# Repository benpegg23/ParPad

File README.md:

# ParPad

**ParPad** is an STM32-based macropad featuring a 3×3 layout and two rotary encoders.  

## Features

- 3×3 mechanical key matrix
- Dual EC11 rotary encoders with push functionality
- Cherry MX switch support
- USB-C connectivity
- STM32F072C8T6 Microcontroller
- Custom firmware (coming soon)

## Images

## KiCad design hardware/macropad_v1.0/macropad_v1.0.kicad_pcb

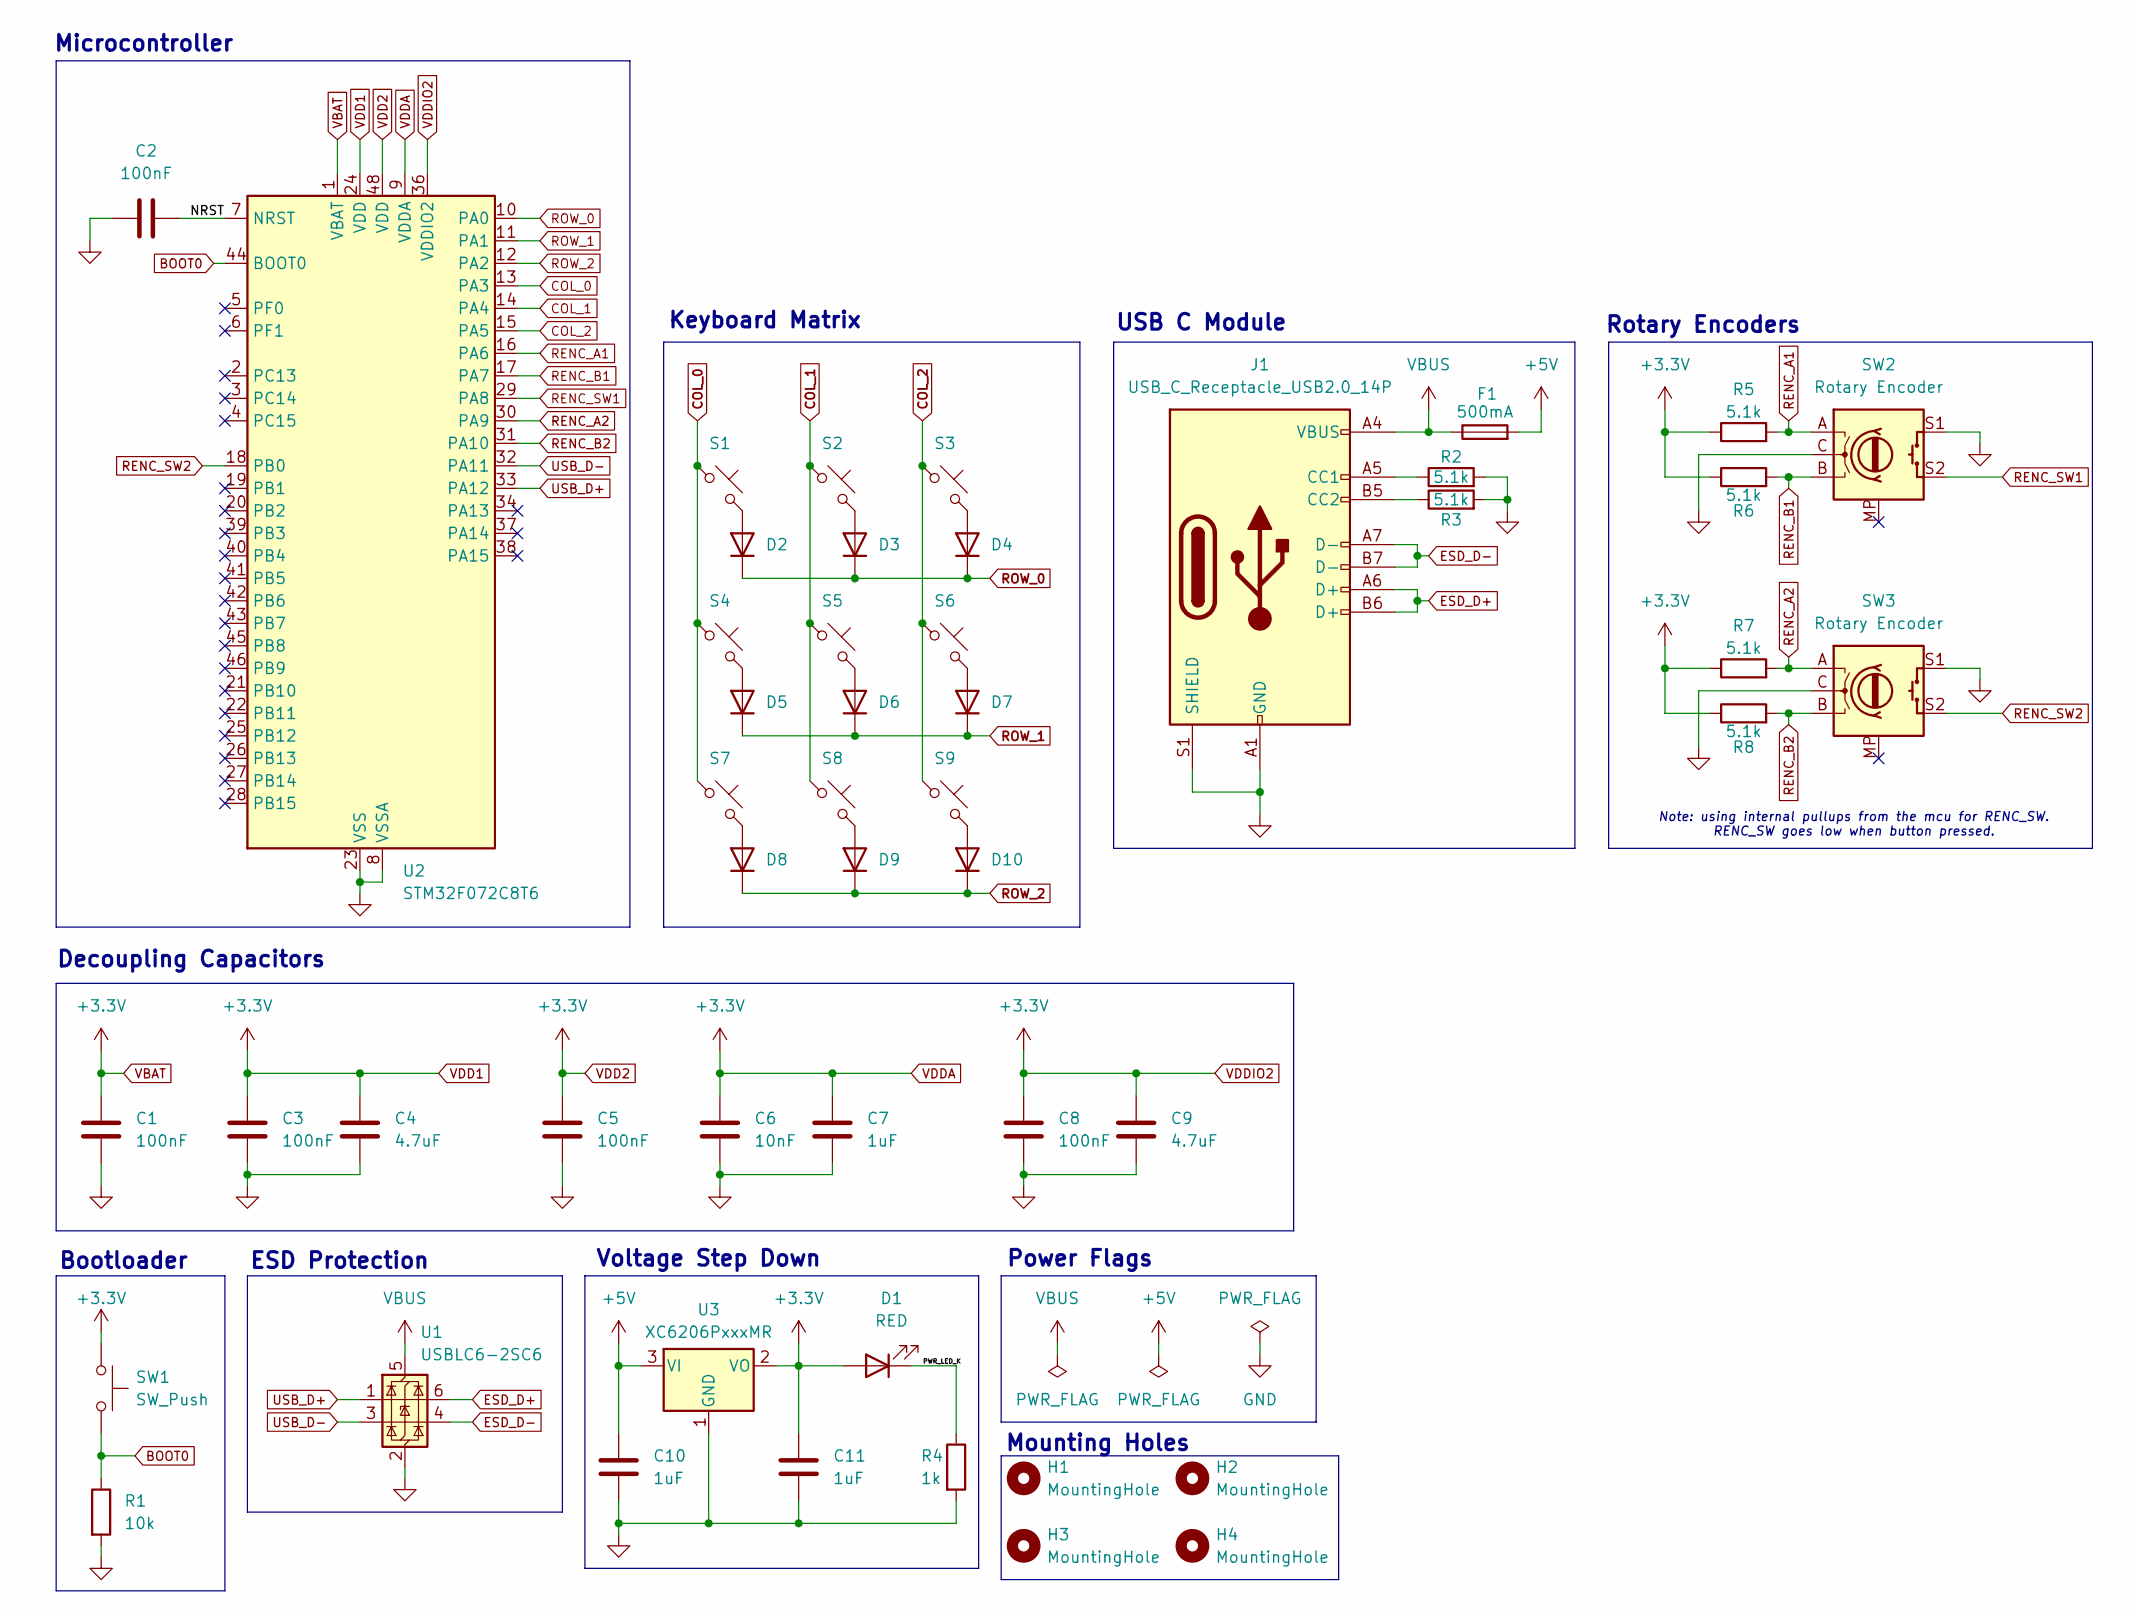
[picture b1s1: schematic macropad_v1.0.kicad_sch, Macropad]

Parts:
C1, C2, C3, C5, C8: 100nF; C_0603_1608Metric_Pad1.08x0.95mm_HandSolder
C4, C9: 4.7uF; C_0603_1608Metric_Pad1.08x0.95mm_HandSolder
C6: 10nF; C_0603_1608Metric_Pad1.08x0.95mm_HandSolder
C7, C10, C11: 1uF; C_0603_1608Metric_Pad1.08x0.95mm_HandSolder
D1: RED; LED_0603_1608Metric_Pad1.05x0.95mm_HandSolder
D2, D3, D4, D5, D6, D7, D8, D9, D10: 1N4148W; D_SOD-123
F1: 500mA; Fuse_1206_3216Metric_Pad1.42x1.75mm_HandSolder
H1, H2, H3, H4: MountingHole; MountingHole_2.2mm_M2
J1: USB_C_Receptacle_USB2.0_14P; USB_C_Receptacle_HRO_TYPE-C-31-M-12
R1: 10k; R_0603_1608Metric_Pad0.98x0.95mm_HandSolder
R2, R3, R5, R6, R7, R8: 5.1k; R_0603_1608Metric_Pad0.98x0.95mm_HandSolder
R4: 1k; R_0603_1608Metric_Pad0.98x0.95mm_HandSolder
S1, S2, S3, S4, S5, S6, S7, S8, S9: Keyswitch; MX_PCB_1.00u
SW1: SW_Push; Button_TL3342
SW2, SW3: Rotary Encoder; RotaryEncoder_Alps_EC11E-Switch_Vertical_H20mm
U1: USBLC6-2SC6; SOT-23-6
U2: STM32F072C8T6; LQFP-48_7x7mm_P0.5mm
U3: XC6206PxxxMR; SOT-23-3

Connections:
+5V: C10.1, F1.2, U3.3 (VI)
/NRST: C2.2, U2.7 (NRST)
/PWR_LED_K: D1.1 (K), R4.1
BOOT0: R1.1, SW1.2, U2.44 (BOOT0)
COL_0: S1.1, S4.1, S7.1, U2.13 (PA3)
COL_1: S2.1, S5.1, S8.1, U2.14 (PA4)
COL_2: S3.1, S6.1, S9.1, U2.15 (PA5)
ESD_D+: J1.A6 (D+), J1.B6 (D+), U1.6 (I/O1)
ESD_D-: J1.A7 (D-), J1.B7 (D-), U1.4 (I/O2)
GND: C1.2, C2.1, C3.2, C4.2, C5.2, C6.2, C7.2, C8.2, C9.2, C10.2, C11.2, J1.A1 (GND), J1.A12 (GND), J1.B1 (GND), J1.B12 (GND), J1.S1 (SHIELD), R1.2, R2.2, R3.2, R4.2, SW2.C, SW2.S1, SW3.C, SW3.S1, U1.2 (GND), U2.8 (VSSA), U2.23 (VSS), U2.35 (VSS), U2.47 (VSS), U3.1 (GND)
unnamed: D2.2 (A), S1.2
unnamed: D3.2 (A), S2.2
unnamed: D4.2 (A), S3.2
unnamed: D5.2 (A), S4.2
unnamed: D6.2 (A), S5.2
unnamed: D7.2 (A), S6.2
unnamed: D8.2 (A), S7.2
unnamed: D9.2 (A), S8.2
unnamed: D10.2 (A), S9.2
unnamed: J1.A5 (CC1), R2.1
unnamed: J1.B5 (CC2), R3.1
RENC_A1: R5.2, SW2.A, U2.16 (PA6)
RENC_A2: R7.2, SW3.A, U2.30 (PA9)
RENC_B1: R6.2, SW2.B, U2.17 (PA7)
RENC_B2: R8.2, SW3.B, U2.31 (PA10)
RENC_SW1: SW2.S2, U2.29 (PA8)
RENC_SW2: SW3.S2, U2.18 (PB0)
ROW_0: D2.1 (K), D3.1 (K), D4.1 (K), U2.10 (PA0)
ROW_1: D5.1 (K), D6.1 (K), D7.1 (K), U2.11 (PA1)
ROW_2: D8.1 (K), D9.1 (K), D10.1 (K), U2.12 (PA2)
USB_D+: U1.1 (I/O1), U2.33 (PA12)
USB_D-: U1.3 (I/O2), U2.32 (PA11)
VBAT: C1.1, C3.1, C4.1, C5.1, C6.1, C7.1, C8.1, C9.1, C11.1, D1.2 (A), R5.1, R6.1, R7.1, R8.1, SW1.1, U2.1 (VBAT), U2.9 (VDDA), U2.24 (VDD), U2.36 (VDDIO2), U2.48 (VDD), U3.2 (VO)
VBUS: F1.1, J1.A4 (VBUS), J1.A9 (VBUS), J1.B4 (VBUS), J1.B9 (VBUS), U1.5 (VBUS)

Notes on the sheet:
Note: using internal pullups from the mcu for RENC_SW. RENC_SW goes low when button pressed.
Voltage Step Down
Keyboard Matrix
Bootloader
Rotary Encoders
Decoupling Capacitors
ESD Protection
Power Flags
USB C Module
Mounting Holes
Microcontroller

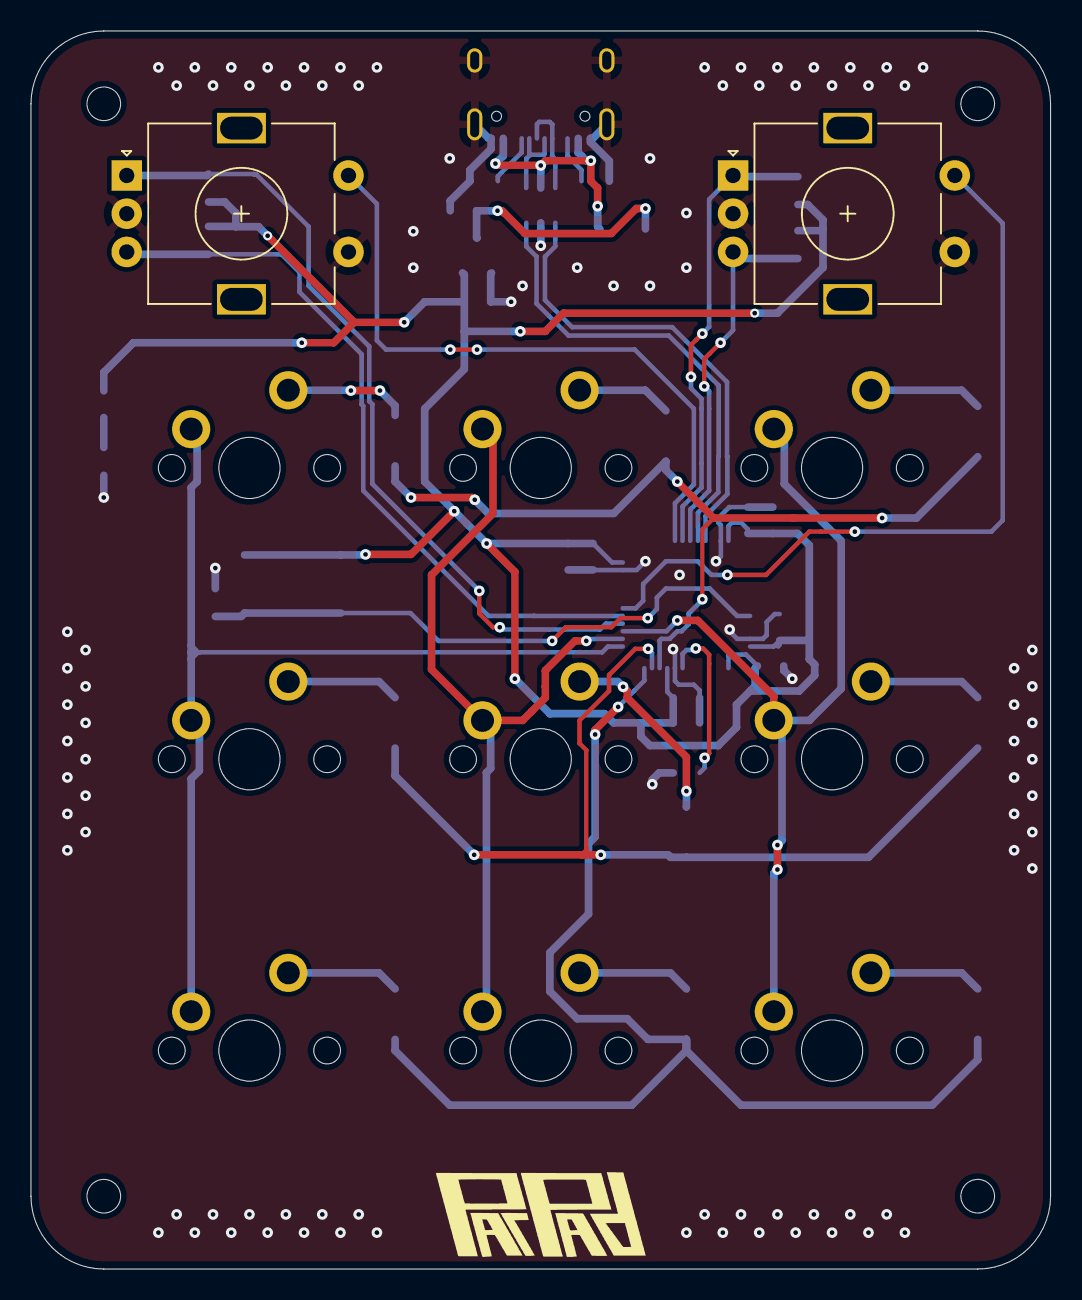
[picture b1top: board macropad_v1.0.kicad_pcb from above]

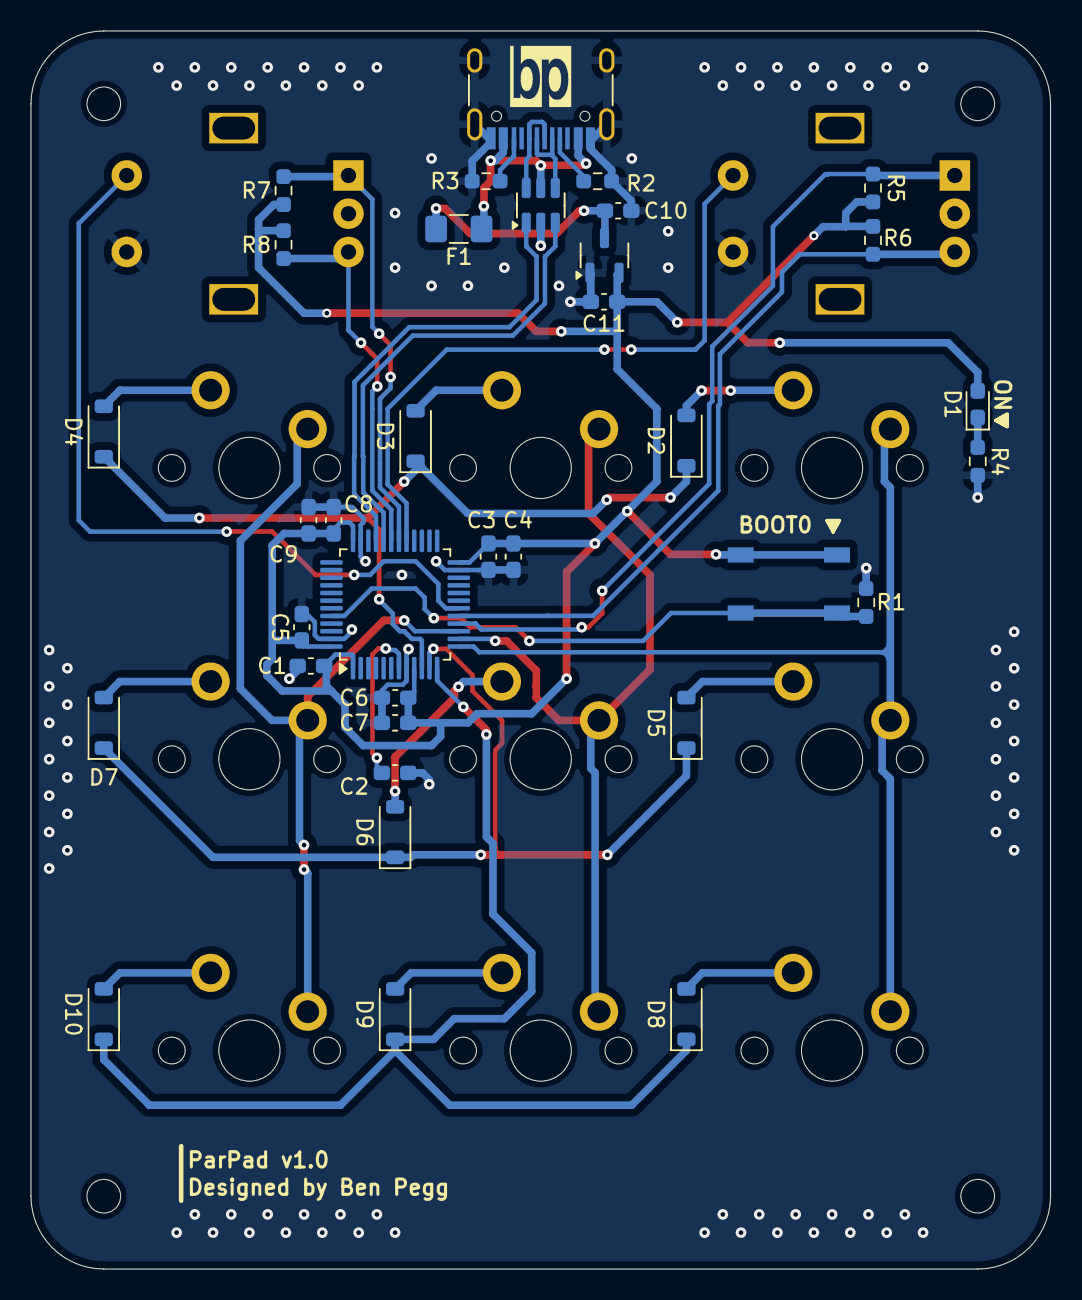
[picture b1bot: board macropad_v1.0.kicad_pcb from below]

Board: 2 copper layers, 66.7 x 81.0 mm, 50 parts (35 on the bottom side), 34 nets.

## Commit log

2025-05-25 pushing initial design of schematic, updated project file structure
2025-05-27 added second rotary encoder, made progress on layout
2025-05-27 finished routing decoupling caps & usb-c module
2025-05-28 updated some 3d models, finished routing usb and esd protection
2025-05-28 finished routing everything except gnd and a few diodes
2025-05-29 routed a bunch of stuff but realized all my vias were the wrong size so I still have to reroute oops
2025-06-02 Deleted old routing, redoing routing
    -Rotated MCU so that datalines are facing upwards towards USB-C receptacle
    -Made sure decoupling capacitors were routed to correct pins on MCU (they weren't before)
    -Corrected minimum via sizing to match JLCPCB rules
    -Cleaned up routing for USB-C receptacle to ESD protection unit to avoid interference from 5V line
    -Next steps should be routing voltage step down so that I can route all the Vdd pins (3.3V)
2025-06-02 Routed voltage step down
2025-06-04 Finished PCB design
    -Routed everything
    -Added a gnd plane to top layer
    Next Steps:
    -Make sure traces are wide enough
    -Move all the silkscreen stuff
    -Check for interference around voltage line
2025-06-05 Finalized Silkscreen
    -Made sure references weren't interfering with pads/vias/etc.
    -Added BP logo to front
    -Moved trace to decap slightly so that it wasn't interfering with mcu silkscreen
    -Added BOOT0 and ON designators to boot button and on diode
    -Added name and designed by to back silkscreen
2025-06-09 Changed USB-C routing
    -Changed routing from usb-c module to esd protection module by shorting the pair of D+ and D- pins. New routing doesn't use a via, has shorter traces from usb module to esd module, and matches the le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
    -Increased the width of the differential pair data traces from esd module to mcu from 0.2mm to 0.3mm to match traces that go into the esd module. Kicad made them 0.2mm by default for some reason.
    -Next steps: change the routing near the MCU to eliminate overuse of vias, add a ground plane to the bottom layer and add stitching vias to connect the two planes
2025-06-10 Changed routing
    -Edited traces to avoid overusing vias
    -Next steps: Add stitching vias to connect the two ground planes
2025-06-10 Added stitching vias
    -Next steps: upload files to jlcpcb, generate a bom, figure out what I'm going to hand-solder, and order everything
2025-06-10 Updated silkscreen and naming stuff, added keepouts
    -Added ParPad logo to fron silkscreen
    -Changed the name of the design in the little design box in the bottom right of the pcb and schematic
    -Added two keepout zones to certain areas of the bottom ground fill to avoid an error about thermal spokes (only had one spoke, just got rid of the spoke cuz the top ground layer already has four spo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
2025-06-10 added basic readme
2025-06-10 small change to readme
2025-06-10 more small changes to readme
2025-06-10 forgot to save schematic
    -exact changes can be found in old commit, I think it was just changing the name in the title block to say ParPad
2025-06-12 Updated stuff according to jlcpcb specifications and added production files
    -Moved the resistors connected to the rotary encoder pins to be further away cuz jlcpcb was mad about tht to smd pad clearance
    -added some more keepouts to bottom gnd plane to get rid of some drc errors about thermal spokes and stuff
    -Moved a via near one of the encoders cuz it was overlapping the silkscreen
    -Moved a couple designators cuz they overlapped with vias
    -Moved C1 (decoupling cap) cuz it was too close to one of the through holes for the switch pins
    -Changed bottom silkscreen to say ParPad instead of PARpad
2025-06-16 updating .gitignore
2025-06-16 updating .gitignore again
2025-06-23 updating readme
2025-07-23 Added hw debugging notes
2025-07-23 Added pictures and updated readme
2025-07-23 Added more debugging notes about finding shorts
2025-08-20 Added more pictures
2025-08-21 added a pic of the layout
